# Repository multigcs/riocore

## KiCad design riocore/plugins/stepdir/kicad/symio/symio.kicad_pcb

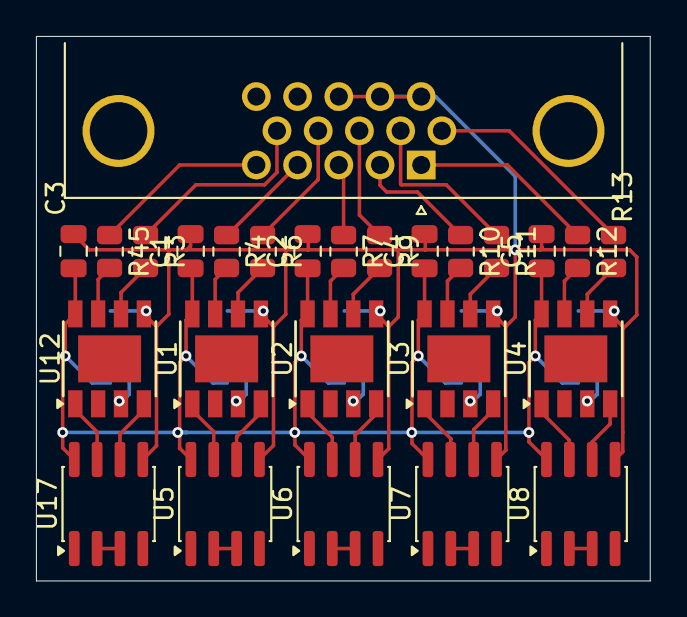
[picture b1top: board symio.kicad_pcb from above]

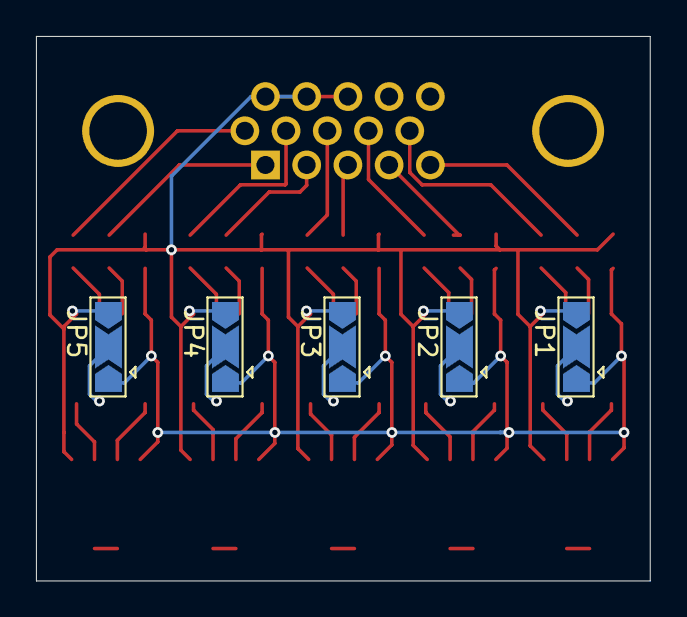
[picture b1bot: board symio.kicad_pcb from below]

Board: 2 copper layers, 34.1 x 30.2 mm, 31 parts (5 on the bottom side), 44 nets.

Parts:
C1, C2, C3, C4, C5: 100n; C_0805_2012Metric
J1: DE15_Pins_HighDensity; DSUB-15-HD_Pins_Horizontal_P2.29x1.90mm_EdgePinOffset3.03mm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
JP1, JP2, JP3, JP4, JP5: SolderJumper_3_Open; SolderJumper-3_P2.0mm_Open_TrianglePad1.0x1.5mm
R3, R4, R6, R7, R9, R10, R11, R12, R13, R45: 100; R_0805_2012Metric
U1, U2, U3, U4, U12: MAX485E; Diodes_SO-8EP
U5, U6, U7, U8, U17: ADuM1201BR; SOIC-8_3.9x4.9mm_P1.27mm

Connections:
3v3: U5.1 (VDD1), U6.1 (VDD1), U7.1 (VDD1), U8.1 (VDD1), U17.1 (VDD1)
/alarm: U7.2 (VOA), U7.3 (VIB)
/dir: U5.2 (VOA), U5.3 (VIB)
/en: U6.2 (VOA), U6.3 (VIB)
/reset: U8.2 (VOA), U8.3 (VIB)
/rw1: JP1.2 (C), U12.2 (~RE), U12.3 (DE)
/rw2: JP2.2 (C), U1.2 (~RE), U1.3 (DE)
/rw3: JP3.2 (C), U2.2 (~RE), U2.3 (DE)
/rw4: JP4.2 (C), U3.2 (~RE), U3.3 (DE)
/rw5: JP5.2 (C), U4.2 (~RE), U4.3 (DE)
/step: U17.2 (VOA), U17.3 (VIB)
F_5V: C1.1, C2.1, C3.1, C4.1, C5.1, J1.15, JP1.1 (A), JP2.1 (A), JP3.1 (A), JP4.1 (A), JP5.1 (A), U1.8 (VCC), U2.8 (VCC), U3.8 (VCC), U4.8 (VCC), U5.8 (VDD2), U6.8 (VDD2), U7.8 (VDD2), U8.8 (VDD2), U12.8 (VCC), U17.8 (VDD2)
F_GND: C1.2, C2.2, C3.2, C4.2, C5.2, J1.11, J1.12, J1.13, JP1.3 (B), JP2.3 (B), JP3.3 (B), JP4.3 (B), JP5.3 (B), U1.5 (GND), U2.5 (GND), U3.5 (GND), U4.5 (GND), U5.5 (GND2), U6.5 (GND2), U7.5 (GND2), U8.5 (GND2), U12.5 (GND), U17.5 (GND2)
GND: U5.4 (GND1), U6.4 (GND1), U7.4 (GND1), U8.4 (GND1), U17.4 (GND1)
unnamed: J1.1, R12.1
unnamed: J1.2, R10.1
unnamed: J1.3, R7.1
unnamed: J1.4, R4.1
unnamed: J1.5, R45.1
unnamed: J1.6, R13.1
unnamed: J1.7, R11.1
unnamed: J1.8, R9.1
unnamed: J1.9, R6.1
unnamed: J1.10, R3.1
unnamed: R6.2, U1.6 (A)
unnamed: R4.2, U1.7 (B)
unnamed: U1.4 (DI), U5.6 (VOB)
unnamed: U1.1 (RO), U5.7 (VIA)
unnamed: R9.2, U2.6 (A)
unnamed: R7.2, U2.7 (B)
unnamed: U2.4 (DI), U6.6 (VOB)
unnamed: U2.1 (RO), U6.7 (VIA)
unnamed: R11.2, U3.6 (A)
unnamed: R10.2, U3.7 (B)
unnamed: U3.4 (DI), U7.6 (VOB)
unnamed: U3.1 (RO), U7.7 (VIA)
unnamed: R13.2, U4.6 (A)
unnamed: R12.2, U4.7 (B)
unnamed: U4.4 (DI), U8.6 (VOB)
unnamed: U4.1 (RO), U8.7 (VIA)
unnamed: R3.2, U12.6 (A)
unnamed: R45.2, U12.7 (B)
unnamed: U12.4 (DI), U17.6 (VOB)
unnamed: U12.1 (RO), U17.7 (VIA)

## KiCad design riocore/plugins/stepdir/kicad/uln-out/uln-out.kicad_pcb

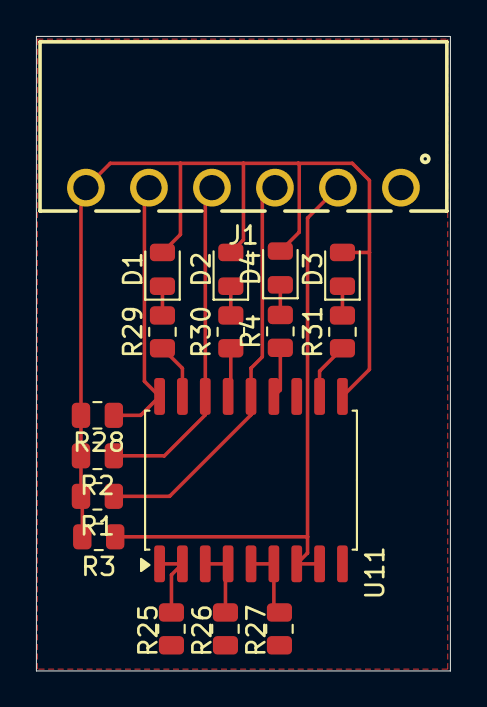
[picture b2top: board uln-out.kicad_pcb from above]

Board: 2 copper layers, 23.0 x 35.2 mm, 17 parts (0 on the bottom side), 17 nets.

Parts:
D1, D2, D3, D4: LED; LED_0805_2012Metric
J1: stepdir; 691322110006
R1, R2, R3, R25, R26, R27, R28: 10k; R_0805_2012Metric
R4, R29, R30, R31: 1k; R_0805_2012Metric
U11: ULN2803A; SOIC-18W_7.5x11.6mm_P1.27mm

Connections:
+5V: D1.2 (A), D2.2 (A), D3.2 (A), D4.2 (A), J1.6, R1.2, R2.2, R3.2, R28.2, U11.10 (COM)
/dir: R26.2, U11.3 (I3), U11.4 (I4)
/en: R27.2, U11.5 (I5), U11.6 (I6)
/step: R25.2, U11.1 (I1), U11.2 (I2)
GND: J1.1, R25.1, R26.1, R27.1, U11.9 (GND)
unnamed: D1.1 (K), R29.2
unnamed: D2.1 (K), R30.2
unnamed: D3.1 (K), R31.2
unnamed: D4.1 (K), R4.2
unnamed: J1.2, R3.1, U11.7 (I7), U11.8 (I8)
unnamed: J1.5, R28.1, U11.18 (O1)
unnamed: R29.1, U11.17 (O2)
unnamed: J1.4, R2.1, U11.16 (O3)
unnamed: R30.1, U11.15 (O4)
unnamed: J1.3, R1.1, U11.14 (O5)
unnamed: R4.1, U11.13 (O6)
unnamed: R31.1, U11.11 (O8)

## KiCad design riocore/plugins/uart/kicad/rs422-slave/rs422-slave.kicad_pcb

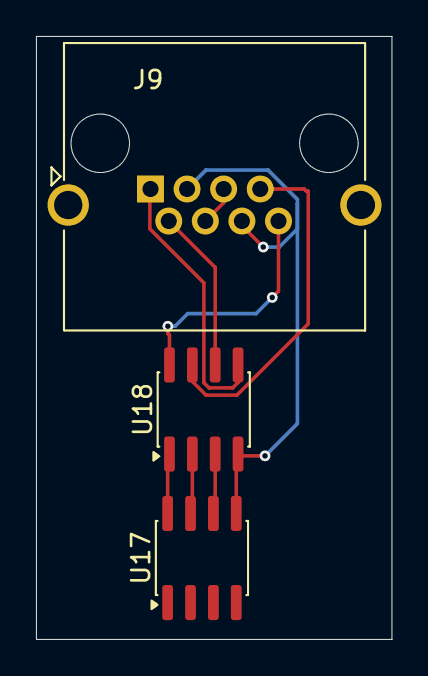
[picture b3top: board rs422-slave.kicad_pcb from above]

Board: 2 copper layers, 19.8 x 33.5 mm, 3 parts (0 on the bottom side), 9 nets.

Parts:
J9: RS422; RJ45_Amphenol_RJHSE5380
U17: ADuM1201BR; SOIC-8_3.9x4.9mm_P1.27mm
U18: ADM3488ExR; SOIC-8_3.9x4.9mm_P1.27mm

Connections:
F_5V: U17.8 (VDD2), U18.1 (VCC)
F_24V: J9.4, J9.5
F_GND: J9.3, J9.6, U17.5 (GND2), U18.4 (GND)
unnamed: U17.7 (VIA), U18.2 (RO)
unnamed: U17.6 (VOB), U18.3 (DI)
unnamed: J9.8, U18.8 (A)
unnamed: J9.7, U18.7 (B)
unnamed: J9.1, U18.5 (Y)
unnamed: J9.2, U18.6 (Z)
